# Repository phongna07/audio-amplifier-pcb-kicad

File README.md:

# LM386 Audio Amplifier PCB (KiCad)

A small mono audio amplifier built around the LM386, designed in KiCad 10 for **Lab 4 – Intro to Circuit** at VinUniversity. Plug a phone or laptop into the 3.5 mm jack, set the volume with the 10k pot, and it drives a 4 Ω / 3 W speaker.

## Previews

### Schematic

### PCB layout

## How it works

- **Input:** the 3.5 mm TRRS jack (J2) has its Tip and Ring 1 tied together, so left and right are summed into one mono signal. Sleeve goes to ground.
- **Volume:** RV1 (10k) works as a voltage divider. Its wiper feeds the LM386 non-inverting input (pin 3); the inverting input (pin 2) is grounded.
- **Gain:** R2 (1k) in series with C3 (10 µF) across the GAIN pins (1 and 8) raises the gain from the default 20 to roughly 50. Remove them for gain 20, or short R2 for gain 200.
- **Output:** C1 (220 µF) blocks the DC offset at VOUT (pin 5) before it reaches the speaker (LS1).
- **Supply:** power comes in on J1. R1 (10 Ω) and C2 (220 µF) form an RC filter on the VS pin (pin 6) to keep supply noise out of the amp. The BYPASS pin (7) is left unconnected.

## Bill of materials

| Ref | Value | Part / footprint |
|-----|-------|------------------|
| U1 | LM386N-1/NOPB | DIP-8 |
| RV1 | 10 kΩ | Trimmer potentiometer |
| R1 | 10 Ω | Axial resistor |
| R2 | 1 kΩ | Axial resistor |
| C1 | 220 µF | Electrolytic, output coupling |
| C2 | 220 µF | Electrolytic, supply decoupling |
| C3 | 10 µF | Electrolytic, gain setting |
| J1 | — | 2-pin header, power (VCC / GND) |
| J2 | AudioJack4 | PJ-320D 3.5 mm jack |
| LS1 | 3 W, 4 Ω | Speaker, 2-pin header |

## Repository contents

| File | Description |
|------|-------------|
| `Lab4_Circuit.kicad_pro` | KiCad project |
| `Lab4_Circuit.kicad_sch` | Schematic |
| `Lab4_Circuit.kicad_pcb` | PCB layout |
| `lm386.kicad_sym` | Custom LM386 symbol |
| `PJ-320D-A--3DModel-STEP-56544.STEP` | 3D model for the audio jack |
| `images/` | Preview images used in this README |

## Opening the project

1. Install [KiCad](https://www.kicad.org/) 10.0 or newer.
2. Clone the repo:
   ```bash
   git clone https://github.com/phongna07/audio-amplifier-pcb-kicad.git
   ```
3. Open `Lab4_Circuit.kicad_pro`.

If the jack shows up without a 3D model, point its footprint's 3D model path at the `.STEP` file in this repo.

## Team

- Nguyen Anh Phong
- Nguyen Hoang Anh
- Duong Nguyen Anh Khoi
- Vu Lai Dung

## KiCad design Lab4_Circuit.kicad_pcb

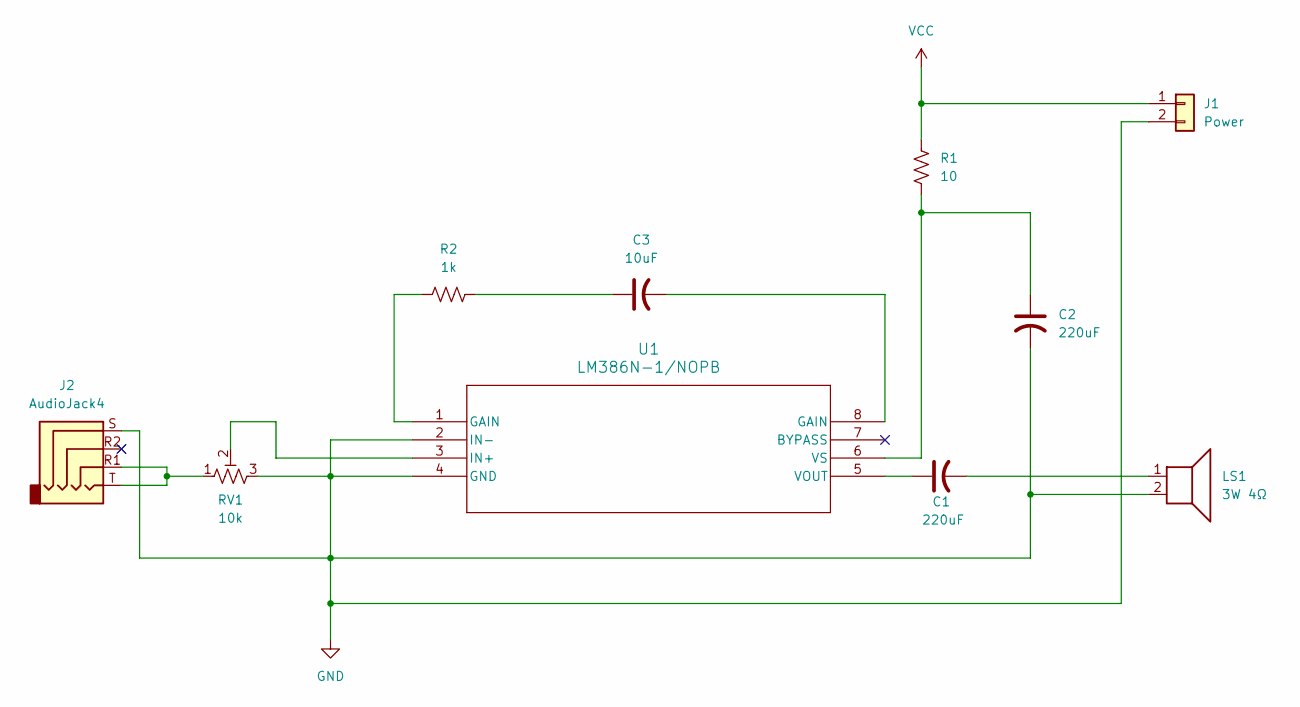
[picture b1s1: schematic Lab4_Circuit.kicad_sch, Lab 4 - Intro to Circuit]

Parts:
C1, C2: 220uF; CP_Radial_D8.0mm_P3.50mm
C3: 10uF; CP_Radial_D5.0mm_P2.00mm
J1: Power; PinHeader_1x02_P2.54mm_Vertical
J2: AudioJack4; Jack_3.5mm_PJ320D_Horizontal
LS1: 3W 4Ω; PinHeader_1x02_P2.54mm_Vertical
R1: 10; R_Axial_DIN0207_L6.3mm_D2.5mm_P7.62mm_Horizontal
R2: 1k; R_Axial_DIN0207_L6.3mm_D2.5mm_P7.62mm_Horizontal
RV1: 10k; Potentiometer_Bourns_3006P_Horizontal
U1: LM386N-1/NOPB; DIP-8_W7.62mm

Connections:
GND: C2.2, J1.2, J2.S, LS1.2, RV1.3, U1.2 (IN-), U1.4 (GND)
unnamed: C1.2, LS1.1
unnamed: C3.1, R2.2
unnamed: C3.2, U1.8 (GAIN)
unnamed: J2.R1, J2.T, RV1.1
unnamed: R2.1, U1.1 (GAIN)
unnamed: RV1.2, U1.3 (IN+)
unnamed: C1.1, U1.5 (VOUT)
unnamed: C2.1, R1.2, U1.6 (VS)
VCC: J1.1, R1.1

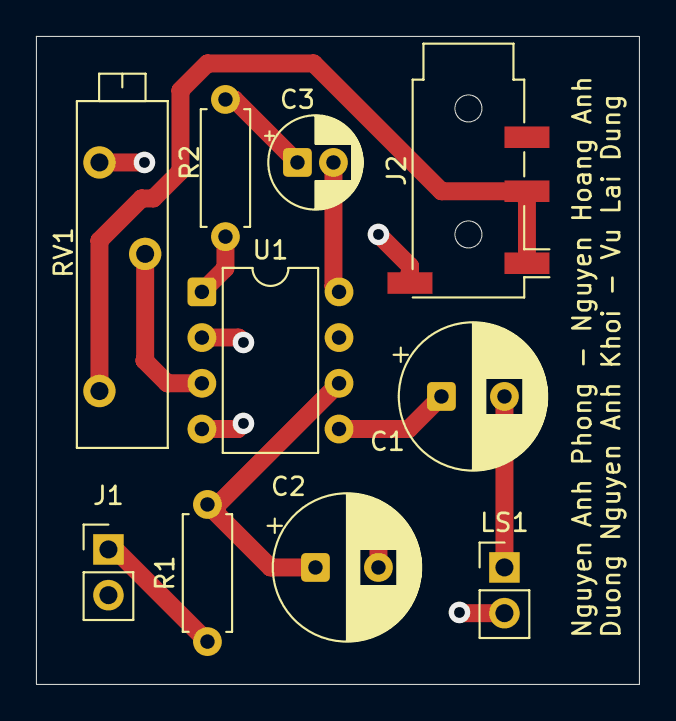
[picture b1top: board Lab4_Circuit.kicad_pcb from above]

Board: 2 copper layers, 33.5 x 36.0 mm, 10 parts (0 on the bottom side), 10 nets.
